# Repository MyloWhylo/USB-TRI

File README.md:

```
    __ __                    __  _______ ____      __________  ____
   / //_/___  _________ _   / / / / ___// __ )    /_  __/ __ \/  _/
  / ,< / __ \/ ___/ __ `/  / / / /\__ \/ __  |_____/ / / /_/ // /  
 / /| / /_/ / /  / /_/ /  / /_/ /___/ / /_/ /_____/ / / _, _// /   
/_/ |_\____/_/   \__, /   \____//____/_____/     /_/ /_/ |_/___/   
                /____/                                             
```

# Korg USB-TRI
A plug-n-play USB sound interface board for the Korg Trinity

# Information
This design is based around the Adafruit QT-PY RP2040 microcontroller. I made this because I was tired of how expensive the actual DI-TRI module is on eBay, and don't want to simply use the analog outputs. So, the USB-TRI module was born.

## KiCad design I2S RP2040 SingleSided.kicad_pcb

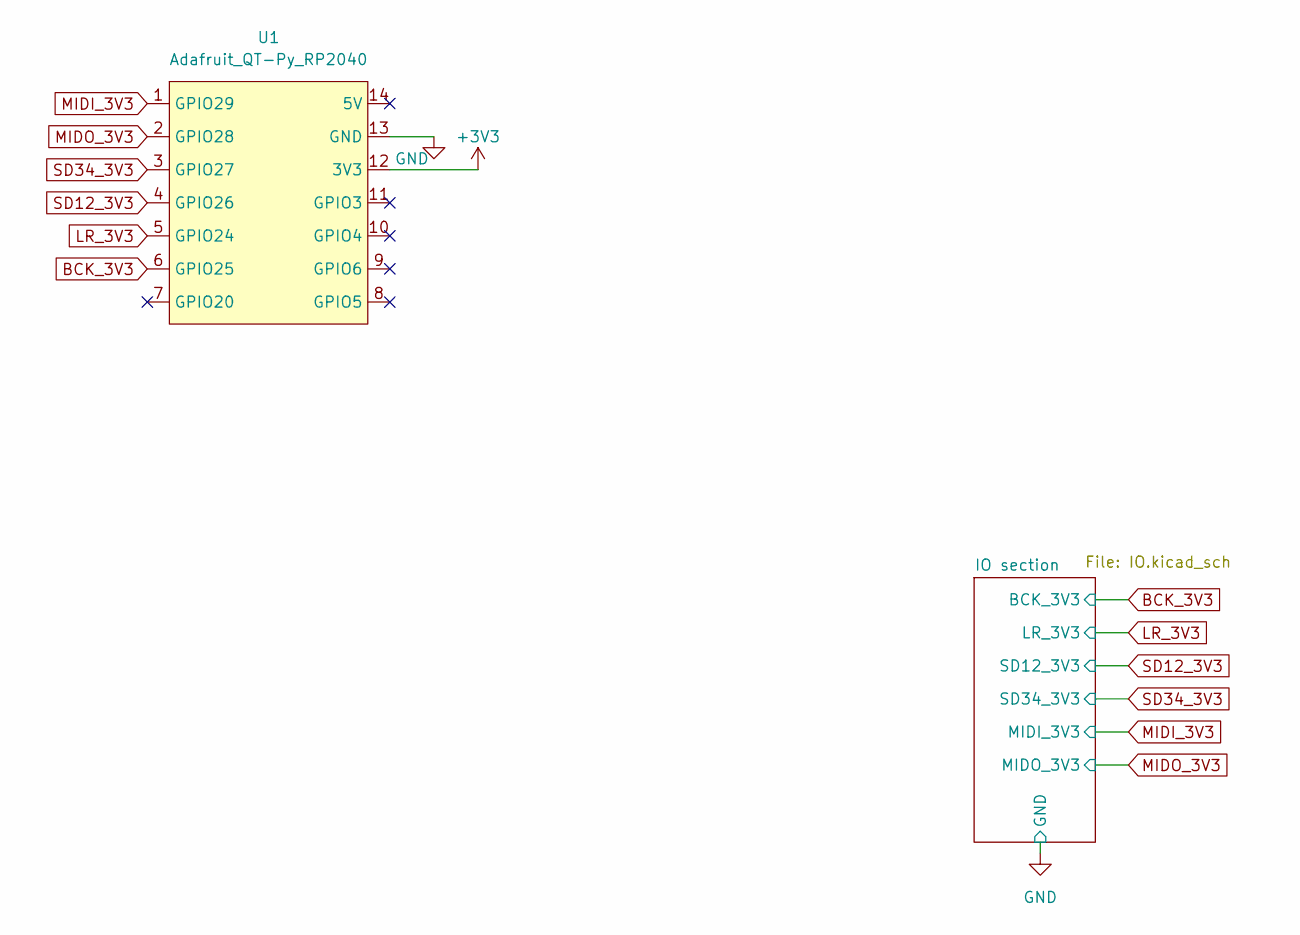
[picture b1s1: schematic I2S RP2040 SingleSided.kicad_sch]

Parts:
U1: Adafruit_QT-Py_RP2040; Adafruit QT-Py RP2040-ThroughHole

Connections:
+3V3: U1.12 (3V3); also elsewhere on the board
BCK_3V3: U1.6 (GPIO25); also elsewhere on the board
GND: U1.13 (GND); also elsewhere on the board
LR_3V3: U1.5 (GPIO24); also elsewhere on the board
MIDI_3V3: U1.1 (GPIO29); also elsewhere on the board
MIDO_3V3: U1.2 (GPIO28); also elsewhere on the board
SD12_3V3: U1.4 (GPIO26); also elsewhere on the board
SD34_3V3: U1.3 (GPIO27); also elsewhere on the board

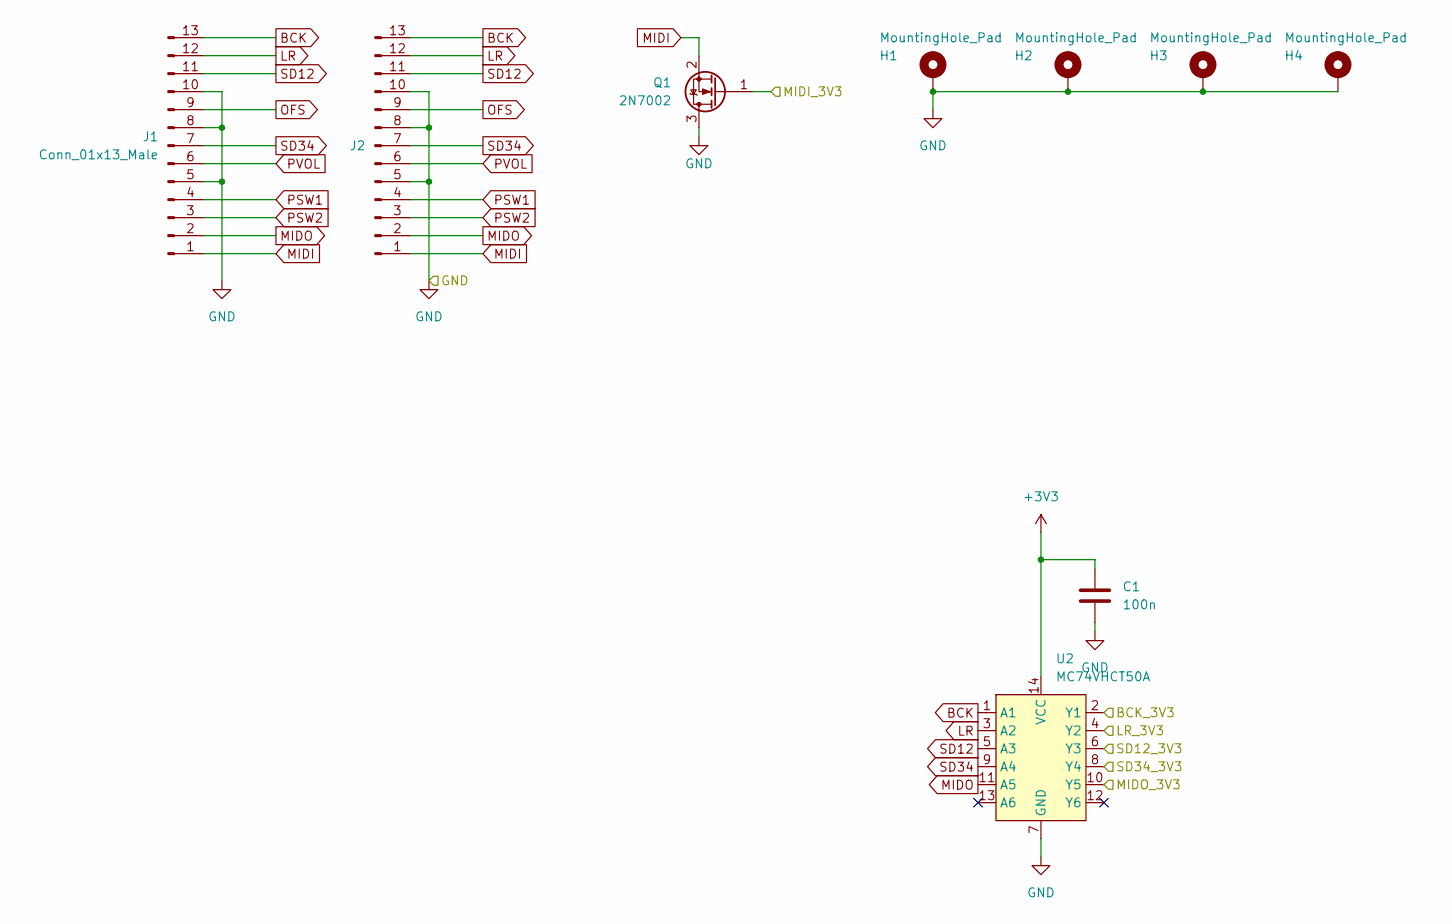
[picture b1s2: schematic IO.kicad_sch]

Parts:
C1: 100n; C_0805_2012Metric_Pad1.18x1.45mm_HandSolder
H1, H2, H3, H4: MountingHole_Pad; MountingHole_3.2mm_M3_Pad_Via
J1, J2: Conn_01x13_Male; JST_PH_B13B-PH-K_1x13_P2.00mm_Vertical
Q1: 2N7002; SOT-23
U2: MC74VHCT50A; TSSOP-14_4.4x5mm_P0.65mm

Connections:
+3V3: C1.1, U2.14 (VCC); also elsewhere on the board
BCK: J1.13, J2.13, U2.1 (A1)
BCK_3V3: U2.2 (Y1); also elsewhere on the board
GND: C1.2, H1.1, H2.1, H3.1, H4.1, J1.5, J1.8, J1.10, J2.5, J2.8, J2.10, Q1.3 (D), U2.7 (GND); also elsewhere on the board
LR: J1.12, J2.12, U2.3 (A2)
LR_3V3: U2.4 (Y2); also elsewhere on the board
MIDI: J1.1, J2.1, Q1.2 (S)
MIDI_3V3: Q1.1 (G); also elsewhere on the board
MIDO: J1.2, J2.2, U2.11 (A5)
MIDO_3V3: U2.10 (Y5); also elsewhere on the board
OFS: J1.9, J2.9
PSW1: J1.4, J2.4
PSW2: J1.3, J2.3
PVOL: J1.6, J2.6
SD12: J1.11, J2.11, U2.5 (A3)
SD12_3V3: U2.6 (Y3); also elsewhere on the board
SD34: J1.7, J2.7, U2.9 (A4)
SD34_3V3: U2.8 (Y4); also elsewhere on the board

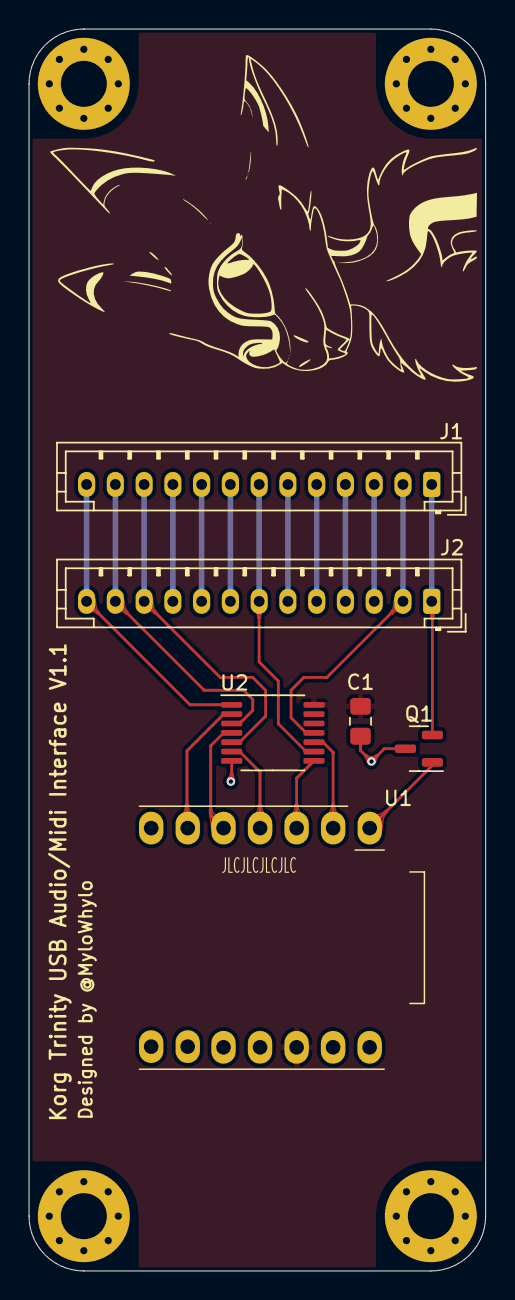
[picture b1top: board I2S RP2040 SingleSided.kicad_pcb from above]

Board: 2 copper layers, 31.8 x 86.4 mm, 10 parts (0 on the bottom side), 18 nets.

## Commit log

2023-02-15 Initial File Upload
2023-02-16 First ReadMe
2023-12-18 Repo cleanup, initial code commit
